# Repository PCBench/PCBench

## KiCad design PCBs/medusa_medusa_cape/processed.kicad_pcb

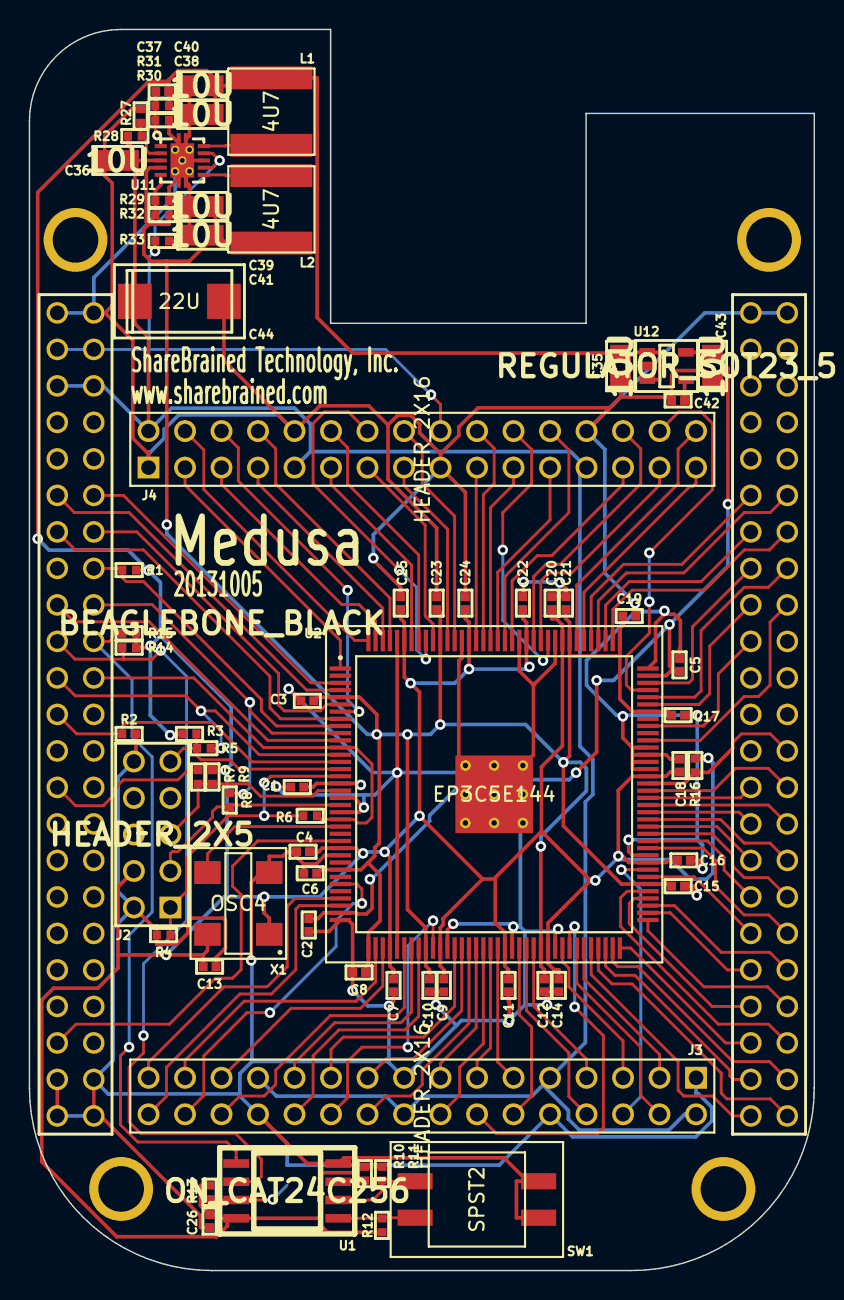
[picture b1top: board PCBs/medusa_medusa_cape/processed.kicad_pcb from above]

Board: 4 copper layers, 54.6 x 86.4 mm, 73 parts (0 on the bottom side), 113 nets.

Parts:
C1, C2, C3, C4, C5, C6, C7, C8, C9, C10, C11, C12, C13, C14, C15, C16, C17, C18, C19, C20, C21, C22, C23, C24, C25, C26: 100N; IPC_CAPC1005X55N
C35, C36, C38, C39, C40, C41, C43: 10U; IPC_CAPC2012X140N
C37: 33P; IPC_CAPC1005X55N
C42: DNI; IPC_CAPC1005X55N
C44: 22U; IPC_CAPMP7343X310N
J1: BEAGLEBONE_BLACK; beaglebone_black
J2: HEADER_2X5; HEADER_5X2_TH_254
J3, J4: HEADER_2X16; HEADER_16X2_TH_254
L1, L2: 4U7; NR6028
R1, R2, R3, R9, R10, R11, R12, R13, R14, R15, R16, R28, R33: 10K; IPC_RESC1005X40N
R4: 1K; IPC_RESC1005X40N
R5, R6, R7, R8, R27: DNI; IPC_RESC1005X40N
R29, R30, R31, R32: R; IPC_RESC1005X40N
SW1: SPST2; 219-2MST
TP1, TP2: TP; TP_1MM
U1: ON_CAT24C256; IPC_SOIC127P780X205-8N
U2: EP3C5E144; QFP50P2200X2200X160-145N_ALTERA
U11: TPS62420; TI_DRC_S-PVSON-N10
U12: REGULATOR_SOT23_5; IPC_SOT95P280X110-5N
X1: OSC4; OSCSC508P500X700X180-4N

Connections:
+1.2V: C3.1, C6.1, C8.1, C10.1, C12.1, C15.1, C17.1, C19.1, C21.1, C23.1, C39.2, C41.2, L2.2, R32.2, U2.5, U2.29, U2.37, U2.45, U2.61, U2.78, U2.102, U2.109, U2.116, U2.134, U11.4
+2.5V: C2.1, C5.1, C43.1, U2.35, U2.107, U12.5
+3.3V: C1.1, C4.1, C7.1, C9.1, C11.1, C13.1, C14.1, C16.1, C18.1, C20.1, C22.1, C24.1, C25.1, C26.1, C35.1, C37.2, C38.1, C40.1, J2.4, L1.1, R1.1, R3.1, R9.1, R10.1, R11.1, R12.1, R13.1, R14.1, R15.1, R16.1, R31.2, U1.8, U2.17, U2.26, U2.40, U2.47, U2.56, U2.62, U2.81, U2.93, U2.117, U2.122, U2.130, U2.139, U12.1, U12.3, X1.1, X1.4
/FPGA/AF0: J3.3, U2.67
/FPGA/AF1: J3.4, U2.66
/FPGA/AF2: J3.5, U2.64
/FPGA/AF3: J3.7, U2.60
/FPGA/AF4: J3.8, U2.59
/FPGA/AF5: J3.11, U2.55
/FPGA/AF6: J3.12, U2.58
/FPGA/AF7: J3.13, U2.54
/FPGA/AF8: J3.15, U2.52
/FPGA/AF9: J3.16, U2.53
/FPGA/AF10: J3.19, U2.50
/FPGA/AF11: J3.20, U2.51
/FPGA/AF12: J3.21, U2.49
/FPGA/AF13: J3.23, U2.43
/FPGA/AF14: J3.24, U2.44
/FPGA/AF15: J3.27, U2.39
/FPGA/AF16: J3.28, U2.42
/FPGA/AF17: J3.29, U2.38
/FPGA/AF18: J3.31, U2.33
/FPGA/AF19: J3.32, U2.34
/FPGA/AS0: J3.6, U2.80
/FPGA/AS1: J3.14, U2.65
/FPGA/AS2: J3.22, U2.46
/FPGA/AS3: J3.30, U2.31
/FPGA/BF0: J4.3, U2.1
/FPGA/BF1: J4.4, U2.144
/FPGA/BF2: J4.5, U2.143
/FPGA/BF3: J4.7, U2.142
/FPGA/BF4: J4.8, U2.141
/FPGA/BF5: J4.11, U2.138
/FPGA/BF6: J4.12, U2.137
/FPGA/BF7: J4.13, U2.135
/FPGA/BF8: J4.15, U2.133
/FPGA/BF9: J4.16, U2.132
/FPGA/BF10: J4.19, U2.129
/FPGA/BF11: J4.20, U2.128
/FPGA/BF12: J4.21, U2.127
/FPGA/BF13: J4.23, U2.126
/FPGA/BF14: J4.24, U2.125
/FPGA/BF15: J4.27, U2.124
/FPGA/BF16: J4.28, U2.121
/FPGA/BF17: J4.29, U2.120
/FPGA/BF18: J4.31, U2.114
/FPGA/BF19: J4.32, U2.115
/FPGA/BS0: J4.6, U2.7
/FPGA/BS1: J4.14, U2.136
/FPGA/BS2: J4.22, U2.119
/FPGA/BS3: J4.30, U2.105
/FPGA/CLKOUT2: J1.B41, U2.25
/FPGA/EHRPWM1A: J1.B14, U2.6
/FPGA/EHRPWM1B: J1.B16, R1.2, U2.9
/FPGA/GPIO1_17: J1.B23, R2.1, U2.14
/FPGA/GPIO1_28: J1.B12, U2.3
/FPGA/GPIO1_29: J1.A26, R16.2, U2.92
/FPGA/GPIO2_1: J1.A18, U2.98
/FPGA/GPIO3_19: J1.B27, R7.2
/FPGA/I2C2_SCL: J1.B19, R14.2, U1.6
/FPGA/I2C2_SDA: J1.B20, R15.2, U1.5
/FPGA/LCD_DATA0: J1.A45, U2.68
/FPGA/LCD_DATA1: J1.A46, U2.69
/FPGA/LCD_DATA2: J1.A43, U2.70
/FPGA/LCD_DATA3: J1.A44, U2.71
/FPGA/LCD_DATA4: J1.A41, U2.72
/FPGA/LCD_DATA5: J1.A42, U2.77
/FPGA/LCD_DATA6: J1.A39, U2.76
/FPGA/LCD_DATA7: J1.A40, U2.73
/FPGA/LCD_DATA8: J1.A37, U2.74
/FPGA/LCD_DATA9: J1.A38, U2.75
/FPGA/LCD_DATA10: J1.A36, U2.83
/FPGA/LCD_DATA11: J1.A34, U2.85
/FPGA/LCD_DATA12: J1.A35, U2.79
/FPGA/LCD_DATA13: J1.A33, U2.84
/FPGA/LCD_DATA14: J1.A31, U2.86
/FPGA/LCD_DATA15: J1.A32, U2.87
/FPGA/LCD_DATA16: J1.A15, U2.106
/FPGA/LCD_DATA17: J1.A16, U2.104
/FPGA/LCD_DATA18: J1.A11, U2.113
/FPGA/LCD_DATA19: J1.A12, U2.112
/FPGA/LCD_DATA20: J1.A17, U2.103
/FPGA/LCD_DATA21: J1.A14, U2.110
/FPGA/LCD_DATA22: J1.A13, U2.111
/FPGA/LCD_DATA23: J1.A19, U2.100
/FPGA/LCD_DE: J1.A30, U2.89
/FPGA/LCD_HSYNC: J1.A29, U2.88
/FPGA/LCD_PCLK: J1.A28, U2.91
/FPGA/LCD_VSYNC: J1.A27, U2.90
/FPGA/PWREN: J1.B3, J1.B4, J4.18, R33.2, U11.7, U11.9
/FPGA/REF_CLK: U2.23, X1.3
/FPGA/SPI0_CS0: J1.B17, U2.11
/FPGA/SPI0_D0: J1.B21, R5.2, U2.13
/FPGA/SPI0_D1: J1.B18, R8.2, U2.10
/FPGA/SPI0_SCLK: J1.B22, R6.2, U2.12, U2.22
/FPGA/TCK: J2.1, R4.1, R6.1, U2.16
/FPGA/TDI: J2.9, R3.2, R5.1, U2.15
/FPGA/TDO: J2.3, R8.1, U2.20
/FPGA/TMS: J2.5, R7.1, R9.2, U2.18
/FPGA/UART4_RXD: J1.B11, U2.4
/FPGA/UART4_TXD: J1.B13, U2.8
/FPGA/V_RAW: C36.1, C44.1, J1.B5, J1.B6, J3.2, J3.9, J3.18, J3.25, J4.2, J4.9, J4.25, R28.1, U11.3
GND: C1.2, C2.2, C3.2, C4.2, C5.2, C6.2, C7.2, C8.2, C9.2, C10.2, C11.2, C12.2, C13.2, C14.2, C15.2, C16.2, C17.2, C18.2, C19.2, C20.2, C21.2, C22.2, C23.2, C24.2, C25.2, C26.2, C35.2, C36.2, C38.2, C39.1, C40.2, C41.1, C42.2, C43.2, C44.2, J1.A1, J1.A2, J1.B1, J1.B2, J1.B43, J1.B44, J1.B45, J1.B46, J2.2, J2.10, J3.1, J3.10, J3.17, J3.26, J4.1, J4.10, J4.17, J4.26, R2.2, R4.2, R27.1, R29.1, R30.1, R33.1, SW1.1, SW1.3, TP2.1, U1.4, U2.19, U2.21, U2.27, U2.36, U2.41, U2.48, U2.57, U2.63, U2.82, U2.94, U2.95, U2.96, U2.97, U2.108, U2.118, U2.123, U2.131, U2.140, U2.PAD, U11.0, U11.8, U12.2, X1.2
Net-<C37-Pad1>: C37.1, R30.2, R31.1, U11.1
Net-<C42-Pad1>: C42.1, U12.4
Net-<L1-Pad2>: L1.2, U11.10
Net-<L2-Pad1>: L2.1, U11.6
Net-<R10-Pad2>: R10.2, U1.3
Net-<R11-Pad2>: R11.2, SW1.4, U1.2
Net-<R12-Pad2>: R12.2, SW1.2, U1.1
Net-<R13-Pad2>: R13.2, TP1.1, U1.7
Net-<R27-Pad2>: R27.2, R28.2, U11.2
Net-<R29-Pad2>: R29.2, R32.1, U11.5

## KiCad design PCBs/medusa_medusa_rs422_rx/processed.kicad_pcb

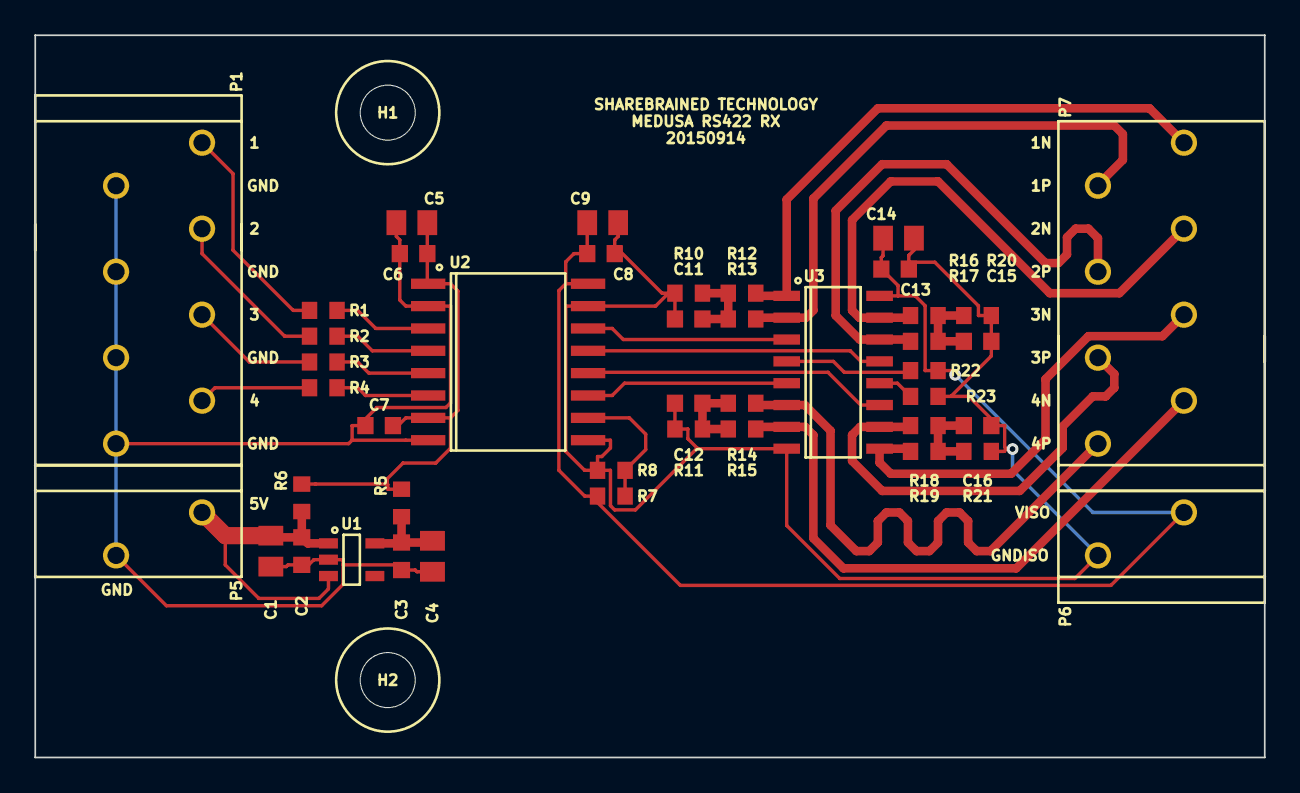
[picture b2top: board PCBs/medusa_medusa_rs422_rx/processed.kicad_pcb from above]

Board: 2 copper layers, 71.5 x 42.0 mm, 46 parts (0 on the bottom side), 33 nets.

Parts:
C1, C4: DNI; IPC_CAPC2012X140N
C2, C3: DNI; IPC_CAPC1608X95N
C5, C9, C14: 10U; IPC_CAPC2012X140N
C6, C7, C8, C13: 100N; IPC_CAPC1608X95N
C11, C12, C15, C16: 10N; IPC_CAPC1608X95N
H1, H2: HOLE; HOLE_3P2MM
P1, P7: TERM8; 1990067
P5, P6: TERM2; 1990009
R1, R2, R3, R4: 22R; IPC_RESC1608X55N
R5, R7, R10, R11, R20, R21: DNI; IPC_RESC1608X55N
R6, R8, R22, R23: 0R; IPC_RESC1608X55N
R12, R13, R14, R15, R16, R17, R18, R19: 50R; IPC_RESC1608X55N
U1: DNI; IPC_SOT95P280X110-5N
U2: ADuM6404; IPC_SOIC127P1030X265-16N
U3: AM26LV32E; IPC_SOIC127P600X175-16N

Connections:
+3.3V: C3.1, C4.1, R5.2, U1.5
+5V: C1.1, C2.1, P5.2, R6.2, U1.1, U1.3
/GNDISO: C8.2, C9.2, C11.1, C12.1, C13.2, C14.2, C15.2, C16.2, P6.2, R8.2, R10.1, R11.1, R20.2, R21.2, R23.2, U2.9, U2.15, U3.8
/RX1: R1.1, U2.3
/RX1ISO: U2.14, U3.3
/RX1N: P7.1, R12.2, U3.1
/RX1P: P7.2, R13.2, U3.2
/RX1R: P1.8, R1.2
/RX2: R2.1, U2.4
/RX2ISO: U2.13, U3.13
/RX2N: P7.3, R16.1, U3.15
/RX2P: P7.4, R17.1, U3.14
/RX2R: P1.6, R2.2
/RX3: R3.1, U2.5
/RX3ISO: U2.12, U3.11
/RX3N: P7.5, R19.1, U3.9
/RX3P: P7.6, R18.1, U3.10
/RX3R: P1.4, R3.2
/RX4: R4.1, U2.6
/RX4ISO: U2.11, U3.5
/RX4N: P7.7, R15.2, U3.7
/RX4P: P7.8, R14.2, U3.6
/RX4R: P1.2, R4.2
/RXG: R22.2, U3.4
/RXG#: R23.1, U3.12
/VDD1: C5.1, C6.1, C7.1, R5.1, R6.1, U2.1, U2.7
/VISO: C8.1, C9.1, C13.1, C14.1, P6.1, R7.2, R22.1, U2.16, U3.16
/VSEL: R7.1, R8.1, U2.10
GND: C1.2, C2.2, C3.2, C4.2, C5.2, C6.2, C7.2, P1.1, P1.3, P1.5, P1.7, P5.1, U1.2, U2.2, U2.8
unnamed: C11.2, R10.2, R12.1, R13.1
unnamed: C12.2, R11.2, R14.1, R15.1
unnamed: C15.1, R16.2, R17.2, R20.1
unnamed: C16.1, R18.2, R19.2, R21.1

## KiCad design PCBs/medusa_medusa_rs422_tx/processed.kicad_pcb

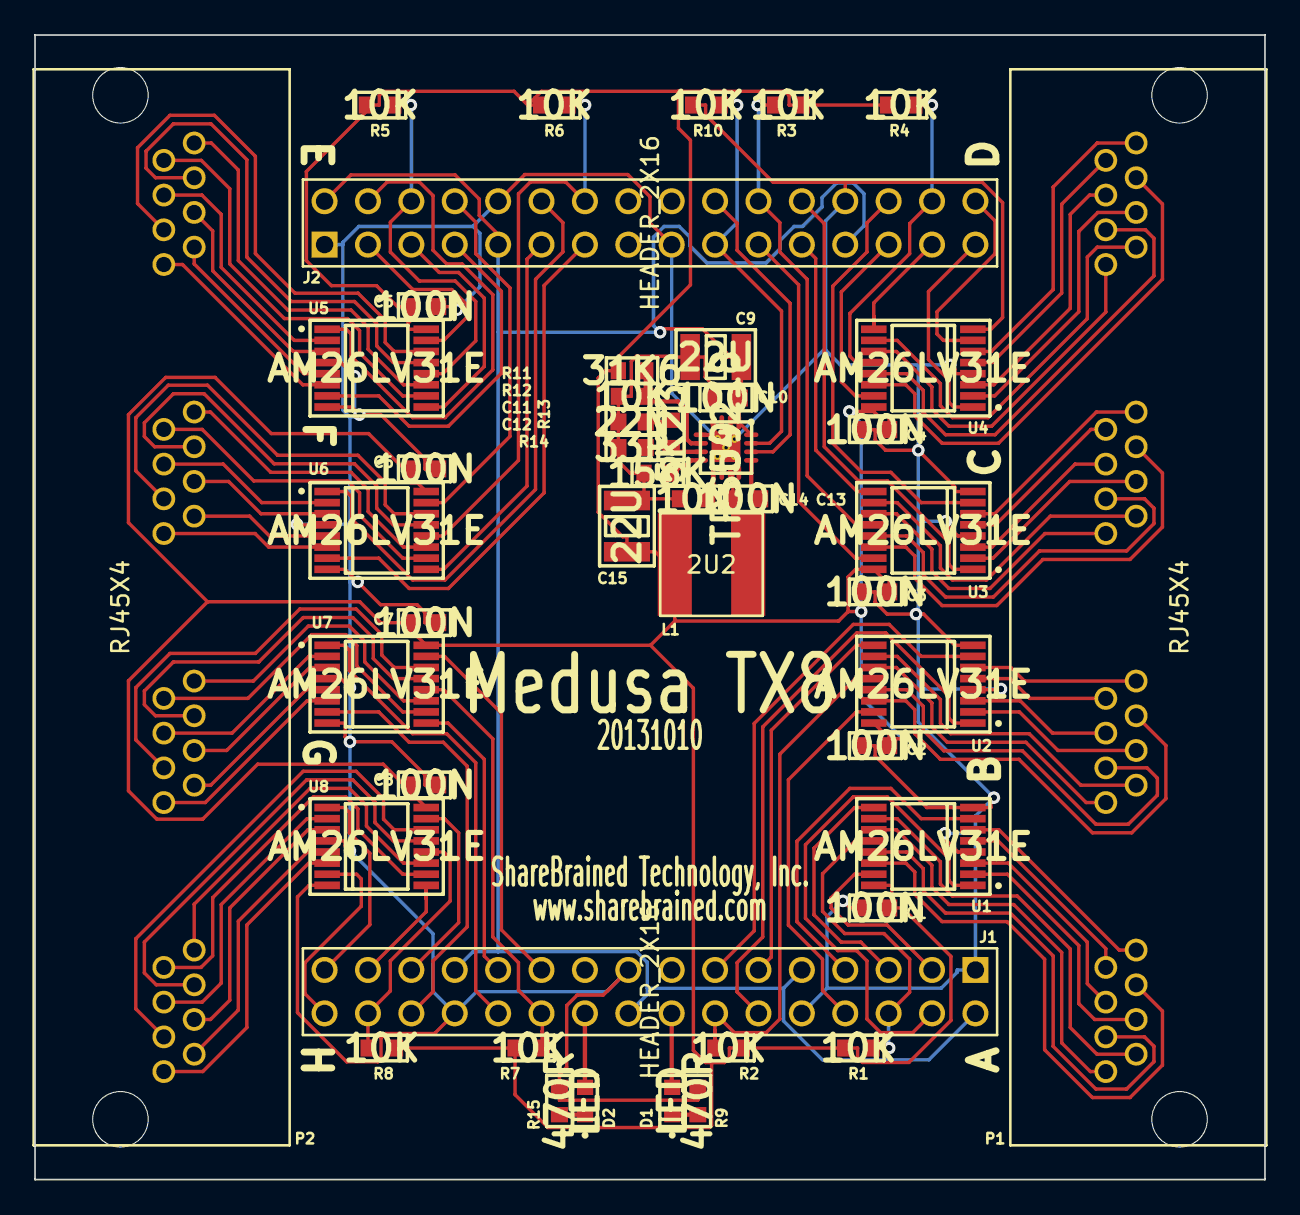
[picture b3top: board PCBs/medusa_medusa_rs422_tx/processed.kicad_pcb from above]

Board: 2 copper layers, 72.0 x 67.0 mm, 46 parts (0 on the bottom side), 120 nets.

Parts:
C1, C2, C3, C4, C5, C6, C7, C8, C10, C13: 100N; IPC_CAPC1608X95N
C9, C15: 22U; IPC_CAPC3225X270N
C11: 22N; IPC_CAPC1608X95N
C12: 33P; IPC_CAPC1608X95N
C14: 10N; IPC_CAPC1608X95N
D1, D2: LED; IPC_LEDC1608X60N
J1, J2: HEADER_2X16; HEADER_16X2_TH_254
L1: 2U2; BOURNS_SRN6045
P1, P2: RJ45X4; AMPHENOL_RJHSE508004
R1, R2, R3, R4, R5, R6, R7, R8, R10, R12: 10K; IPC_RESC1608X55N
R9, R15: 470R; IPC_RESC1608X55N
R11: 31K6; IPC_RESC1608X55N
R13: 5K23; IPC_RESC1608X55N
R14: 158K; IPC_RESC1608X55N
U1, U2, U3, U4, U5, U6, U7, U8: AM26LV31E; IPC_SOP65P640X120-16N
U9: TPS54218; TI_RTE_S-PWQFN-N16

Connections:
/AF0: J1.3, U1.15
/AF1: J1.4, U1.1
/AF2: J1.5, U1.9
/AF3: J1.7, U1.7
/AF4: J1.8, U2.15
/AF5: J1.11, U2.9
/AF6: J1.12, U2.1
/AF7: J1.13, U2.7
/AF9: D1.1, J1.16
/AF11: D2.1, J1.20
/AF12: J1.21, U7.15
/AF13: J1.23, U7.9
/AF14: J1.24, U7.1
/AF15: J1.27, U8.15
/AF16: J1.28, U7.7
/AF17: J1.29, U8.9
/AF18: J1.31, U8.1
/AF19: J1.32, U8.7
/AS0: J1.6, R1.1, U1.12
/AS1: J1.14, R2.1, U2.12
/AS2: J1.22, R7.1, U7.12
/AS3: J1.30, R8.1, U8.12
/BF0: J2.3, U5.15
/BF1: J2.4, U5.1
/BF2: J2.5, U5.9
/BF3: J2.7, U5.7
/BF4: J2.8, U6.15
/BF5: J2.11, U6.9
/BF6: J2.12, U6.1
/BF7: J2.13, U6.7
/BF10: J2.19, R10.2, U9.15
/BF11: J2.20, U9.14
/BF12: J2.21, U3.15
/BF13: J2.23, U3.9
/BF14: J2.24, U3.1
/BF15: J2.27, U4.15
/BF16: J2.28, U3.7
/BF17: J2.29, U4.9
/BF18: J2.31, U4.1
/BF19: J2.32, U4.7
/BS0: J2.6, R5.1, U5.12
/BS1: J2.14, R6.1, U6.12
/BS2: J2.22, R3.1, U3.12
/BS3: J2.30, R4.1, U4.12
/SWPH: C13.2, L1.2, U9.10, U9.11, U9.12
/TX0N: P1.A2, U1.5
/TX0P: P1.A1, U1.6
/TX1N: P1.A6, U1.13
/TX1P: P1.A3, U1.14
/TX2N: P1.A4, U1.3
/TX2P: P1.A5, U1.2
/TX3N: P1.A8, U1.11
/TX3P: P1.A7, U1.10
/TX4N: P1.B2, U2.5
/TX4P: P1.B1, U2.6
/TX5N: P1.B6, U2.13
/TX5P: P1.B3, U2.14
/TX6N: P1.B4, U2.3
/TX6P: P1.B5, U2.2
/TX7N: P1.B8, U2.11
/TX7P: P1.B7, U2.10
/TX8N: P1.C2, U3.5
/TX8P: P1.C1, U3.6
/TX9N: P1.C6, U3.13
/TX9P: P1.C3, U3.14
/TX10N: P1.C4, U3.3
/TX10P: P1.C5, U3.2
/TX11N: P1.C8, U3.11
/TX11P: P1.C7, U3.10
/TX12N: P1.D2, U4.5
/TX12P: P1.D1, U4.6
/TX13N: P1.D6, U4.13
/TX13P: P1.D3, U4.14
/TX14N: P1.D4, U4.3
/TX14P: P1.D5, U4.2
/TX15N: P1.D8, U4.11
/TX15P: P1.D7, U4.10
/TX16N: P2.A2, U5.5
/TX16P: P2.A1, U5.6
/TX17N: P2.A6, U5.13
/TX17P: P2.A3, U5.14
/TX18N: P2.A4, U5.3
/TX18P: P2.A5, U5.2
/TX19N: P2.A8, U5.11
/TX19P: P2.A7, U5.10
/TX20N: P2.B2, U6.5
/TX20P: P2.B1, U6.6
/TX21N: P2.B6, U6.13
/TX21P: P2.B3, U6.14
/TX22N: P2.B4, U6.3
/TX22P: P2.B5, U6.2
/TX23N: P2.B8, U6.11
/TX23P: P2.B7, U6.10
/TX24N: P2.C2, U7.5
/TX24P: P2.C1, U7.6
/TX25N: P2.C6, U7.13
/TX25P: P2.C3, U7.14
/TX26N: P2.C4, U7.3
/TX26P: P2.C5, U7.2
/TX27N: P2.C8, U7.11
/TX27P: P2.C7, U7.10
/TX28N: P2.D2, U8.5
/TX28P: P2.D1, U8.6
/TX29N: P2.D6, U8.13
/TX29P: P2.D3, U8.14
/TX30N: P2.D4, U8.3
/TX30P: P2.D5, U8.2
/TX31N: P2.D8, U8.11
/TX31P: P2.D7, U8.10
/VTX: C1.1, C2.1, C3.1, C4.1, C5.1, C6.1, C7.1, C8.1, C15.1, L1.1, R1.2, R2.2, R3.2, R4.2, R5.2, R6.2, R7.2, R8.2, R11.1, U1.16, U2.16, U3.16, U4.16, U5.16, U6.16, U7.16, U8.16
/V_RAW: C9.1, C10.1, J1.2, J1.9, J1.18, J1.25, J2.2, J2.9, J2.25, U9.1, U9.2, U9.16
GND: C1.2, C2.2, C3.2, C4.2, C5.2, C6.2, C7.2, C8.2, C9.2, C10.2, C11.2, C12.2, C14.2, C15.2, J1.1, J1.10, J1.17, J1.26, J2.1, J2.10, J2.17, J2.26, R9.1, R10.1, R12.1, R14.1, R15.1, U1.4, U1.8, U2.4, U2.8, U3.4, U3.8, U4.4, U4.8, U5.4, U5.8, U6.4, U6.8, U7.4, U7.8, U8.4, U8.8, U9.3, U9.4, U9.5, U9.17
Net-<C11-Pad1>: C11.1, R13.1
Net-<C12-Pad1>: C12.1, R13.2, U9.7
Net-<C13-Pad1>: C13.1, U9.13
Net-<C14-Pad1>: C14.1, U9.9
Net-<D1-Pad2>: D1.2, R9.2
Net-<D2-Pad2>: D2.2, R15.2
Net-<R11-Pad2>: R11.2, R12.2, U9.6
Net-<R14-Pad2>: R14.2, U9.8

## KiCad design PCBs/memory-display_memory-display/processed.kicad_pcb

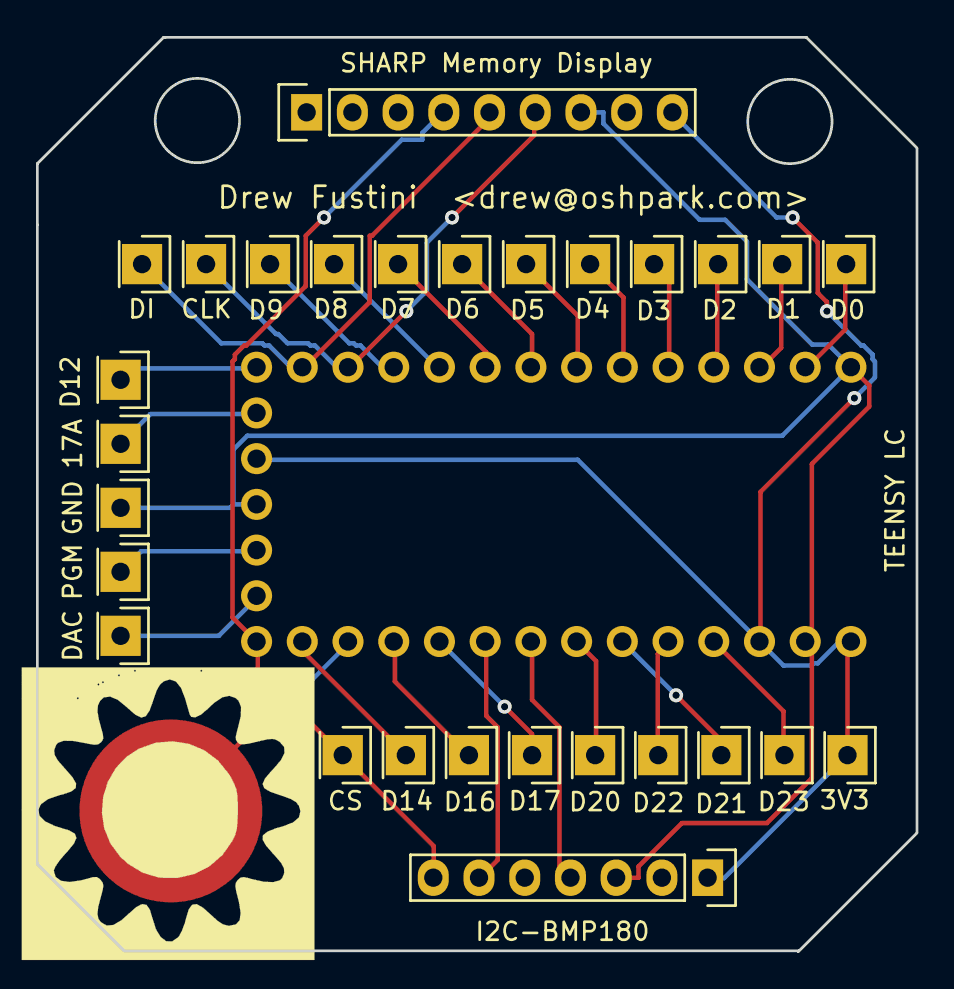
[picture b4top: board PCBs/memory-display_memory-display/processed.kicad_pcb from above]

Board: 2 copper layers, 48.9 x 50.8 mm, 30 parts (0 on the bottom side), 29 nets.

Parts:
3V3: 3v3; CONN-HEADER-STRAIGHT-P2.54MM-1x01
17A: 17A; CONN-HEADER-STRAIGHT-P2.54MM-1x01
CAP15: CAP15; CAPSENSE-CIRCLE-D10MM
CLK: CLK; CONN-HEADER-STRAIGHT-P2.54MM-1x01
CS: CS; CONN-HEADER-STRAIGHT-P2.54MM-1x01
D0: D0; CONN-HEADER-STRAIGHT-P2.54MM-1x01
D1: D1; CONN-HEADER-STRAIGHT-P2.54MM-1x01
D2: D2; CONN-HEADER-STRAIGHT-P2.54MM-1x01
D3: D3; CONN-HEADER-STRAIGHT-P2.54MM-1x01
D4: D4; CONN-HEADER-STRAIGHT-P2.54MM-1x01
D5: D5; CONN-HEADER-STRAIGHT-P2.54MM-1x01
D6: D6; CONN-HEADER-STRAIGHT-P2.54MM-1x01
D7: D7; CONN-HEADER-STRAIGHT-P2.54MM-1x01
D8: D8; CONN-HEADER-STRAIGHT-P2.54MM-1x01
D9: D9; CONN-HEADER-STRAIGHT-P2.54MM-1x01
D12: D12; CONN-HEADER-STRAIGHT-P2.54MM-1x01
D14: D14; CONN-HEADER-STRAIGHT-P2.54MM-1x01
D16: D16; CONN-HEADER-STRAIGHT-P2.54MM-1x01
D17: D17; CONN-HEADER-STRAIGHT-P2.54MM-1x01
D20: D20; CONN-HEADER-STRAIGHT-P2.54MM-1x01
D21: D21; CONN-HEADER-STRAIGHT-P2.54MM-1x01
D22: D22; CONN-HEADER-STRAIGHT-P2.54MM-1x01
D23: D23; CONN-HEADER-STRAIGHT-P2.54MM-1x01
DAC: DAC; CONN-HEADER-STRAIGHT-P2.54MM-1x01
DI: DI; CONN-HEADER-STRAIGHT-P2.54MM-1x01
GND: PGM; CONN-HEADER-STRAIGHT-P2.54MM-1x01
I2C-BMP180: I2C-BMP180; Pin_Header_Straight_1x07
J1: TEENSY-LC
PGM: PGM; CONN-HEADER-STRAIGHT-P2.54MM-1x01
SHARP Memory Display: SHARP-MEM-DISP; Pin_Header_Straight_1x09

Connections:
+3V3: 3V3.1, I2C-BMP180.1, J1.3V1, J1.3V2, J1.VIN, SHARP Memory Display.9
/CLK: CLK.1, J1.10, SHARP Memory Display.6
/CS: CS.1, I2C-BMP180.7, J1.13, SHARP Memory Display.4
/D0: D0.1, J1.0
/D1: D1.1, J1.1
/D2: D2.1, J1.2
/D3: D3.1, J1.3
/D4: D4.1, J1.4
/D5: D5.1, J1.5
/D6: D6.1, J1.6
/D7: D7.1, J1.7
/D8: D8.1, J1.8
/D9: D9.1, J1.9
/D11: DI.1, J1.11, SHARP Memory Display.5
/D12: D12.1, J1.12
/D14: D14.1, J1.14
/D15: CAP15.1, J1.15
/D16: D16.1, J1.16
/D17: D17.1, J1.17
/D17(VIN): 17A.1, J1.17A
/D18: I2C-BMP180.6, J1.18
/D19: I2C-BMP180.4, J1.19
/D20: D20.1, J1.20
/D21: D21.1, J1.21
/D22: D22.1, J1.22
/D23: D23.1, J1.23
/DAC: DAC.1, J1.DAC
/PROG: J1.PGM, PGM.1
GND: GND.1, I2C-BMP180.3, J1.G1, J1.G2, J1.G3, SHARP Memory Display.7

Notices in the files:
PCBs/memory-display_memory-display/processed.kicad_pcb:
Released under the CERN Open Hardware License v1.2
